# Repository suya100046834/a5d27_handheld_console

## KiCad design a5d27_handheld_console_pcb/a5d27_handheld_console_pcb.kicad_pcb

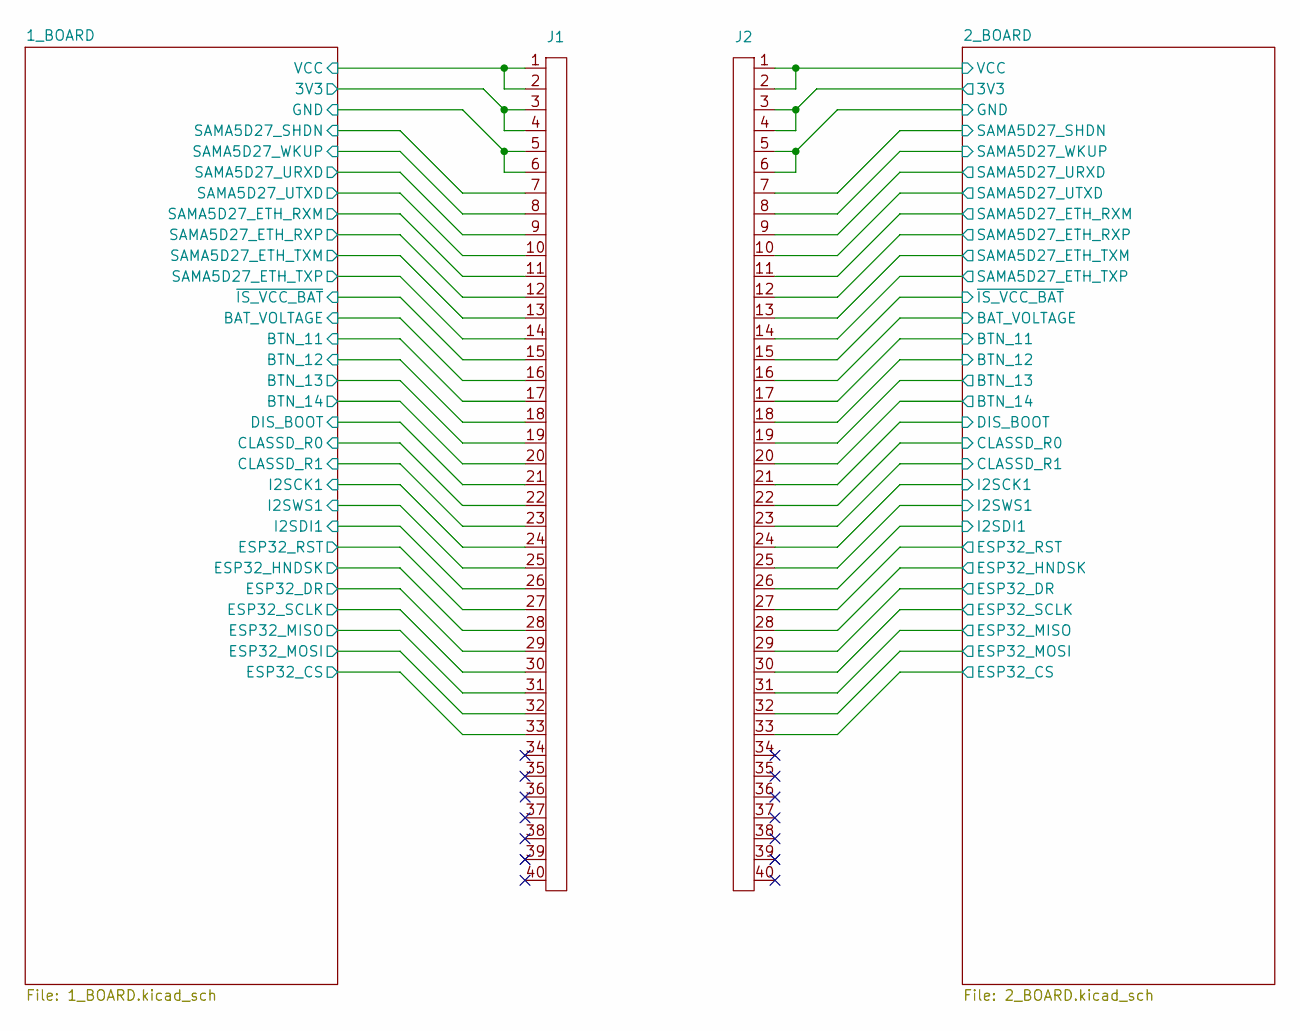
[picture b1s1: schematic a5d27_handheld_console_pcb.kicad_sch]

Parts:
J1: CONN_MALE
J2: CONN_FEMALE

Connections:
3V3_1: J1.3, J1.4; also elsewhere on the board
3V3_2: J2.3, J2.4; also elsewhere on the board
/1_BOARD/BAT_VOLTAGE: J1.16; also elsewhere on the board
/1_BOARD/BTN_11: J1.17; also elsewhere on the board
/1_BOARD/BTN_12: J1.18; also elsewhere on the board
/1_BOARD/BTN_13: J1.19; also elsewhere on the board
/1_BOARD/BTN_14: J1.20; also elsewhere on the board
/1_BOARD/CLASSD_R0: J1.22; also elsewhere on the board
/1_BOARD/CLASSD_R1: J1.23; also elsewhere on the board
/1_BOARD/DIS_BOOT: J1.21; also elsewhere on the board
/1_BOARD/ESP32_CS: J1.33; also elsewhere on the board
/1_BOARD/ESP32_DR: J1.29; also elsewhere on the board
/1_BOARD/ESP32_HNDSK: J1.28; also elsewhere on the board
/1_BOARD/ESP32_MISO: J1.31; also elsewhere on the board
/1_BOARD/ESP32_MOSI: J1.32; also elsewhere on the board
/1_BOARD/ESP32_RST: J1.27; also elsewhere on the board
/1_BOARD/ESP32_SCLK: J1.30; also elsewhere on the board
/1_BOARD/I2SCK1: J1.24; also elsewhere on the board
/1_BOARD/I2SDI1: J1.26; also elsewhere on the board
/1_BOARD/I2SWS1: J1.25; also elsewhere on the board
/1_BOARD/SAMA5D27_ETH_RXM: J1.11; also elsewhere on the board
/1_BOARD/SAMA5D27_ETH_RXP: J1.12; also elsewhere on the board
/1_BOARD/SAMA5D27_ETH_TXM: J1.13; also elsewhere on the board
/1_BOARD/SAMA5D27_ETH_TXP: J1.14; also elsewhere on the board
/1_BOARD/SAMA5D27_SHDN: J1.7; also elsewhere on the board
/1_BOARD/SAMA5D27_URXD: J1.9; also elsewhere on the board
/1_BOARD/SAMA5D27_UTXD: J1.10; also elsewhere on the board
/1_BOARD/SAMA5D27_WKUP: J1.8; also elsewhere on the board
/1_BOARD/~IS_VCC_BAT: J1.15; also elsewhere on the board
/2_BOARD/BAT_VOLTAGE: J2.16; also elsewhere on the board
/2_BOARD/BTN_11: J2.17; also elsewhere on the board
/2_BOARD/BTN_12: J2.18; also elsewhere on the board
/2_BOARD/BTN_13: J2.19; also elsewhere on the board
/2_BOARD/BTN_14: J2.20; also elsewhere on the board
/2_BOARD/CLASSD_R0: J2.22; also elsewhere on the board
/2_BOARD/CLASSD_R1: J2.23; also elsewhere on the board
/2_BOARD/DIS_BOOT: J2.21; also elsewhere on the board
/2_BOARD/ESP32_CS: J2.33; also elsewhere on the board
/2_BOARD/ESP32_DR: J2.29; also elsewhere on the board
/2_BOARD/ESP32_HNDSK: J2.28; also elsewhere on the board
/2_BOARD/ESP32_MISO: J2.31; also elsewhere on the board
/2_BOARD/ESP32_MOSI: J2.32; also elsewhere on the board
/2_BOARD/ESP32_RST: J2.27; also elsewhere on the board
/2_BOARD/ESP32_SCLK: J2.30; also elsewhere on the board
/2_BOARD/I2SCK1: J2.24; also elsewhere on the board
/2_BOARD/I2SDI1: J2.26; also elsewhere on the board
/2_BOARD/I2SWS1: J2.25; also elsewhere on the board
/2_BOARD/SAMA5D27_ETH_RXM: J2.11; also elsewhere on the board
/2_BOARD/SAMA5D27_ETH_RXP: J2.12; also elsewhere on the board
/2_BOARD/SAMA5D27_ETH_TXM: J2.13; also elsewhere on the board
/2_BOARD/SAMA5D27_ETH_TXP: J2.14; also elsewhere on the board
/2_BOARD/SAMA5D27_SHDN: J2.7; also elsewhere on the board
/2_BOARD/SAMA5D27_URXD: J2.9; also elsewhere on the board
/2_BOARD/SAMA5D27_UTXD: J2.10; also elsewhere on the board
/2_BOARD/SAMA5D27_WKUP: J2.8; also elsewhere on the board
/2_BOARD/~IS_VCC_BAT: J2.15; also elsewhere on the board
GND_1: J1.5, J1.6; also elsewhere on the board
GND_2: J2.5, J2.6; also elsewhere on the board
VCC_1: J1.1, J1.2; also elsewhere on the board
VCC_2: J2.1, J2.2; also elsewhere on the board

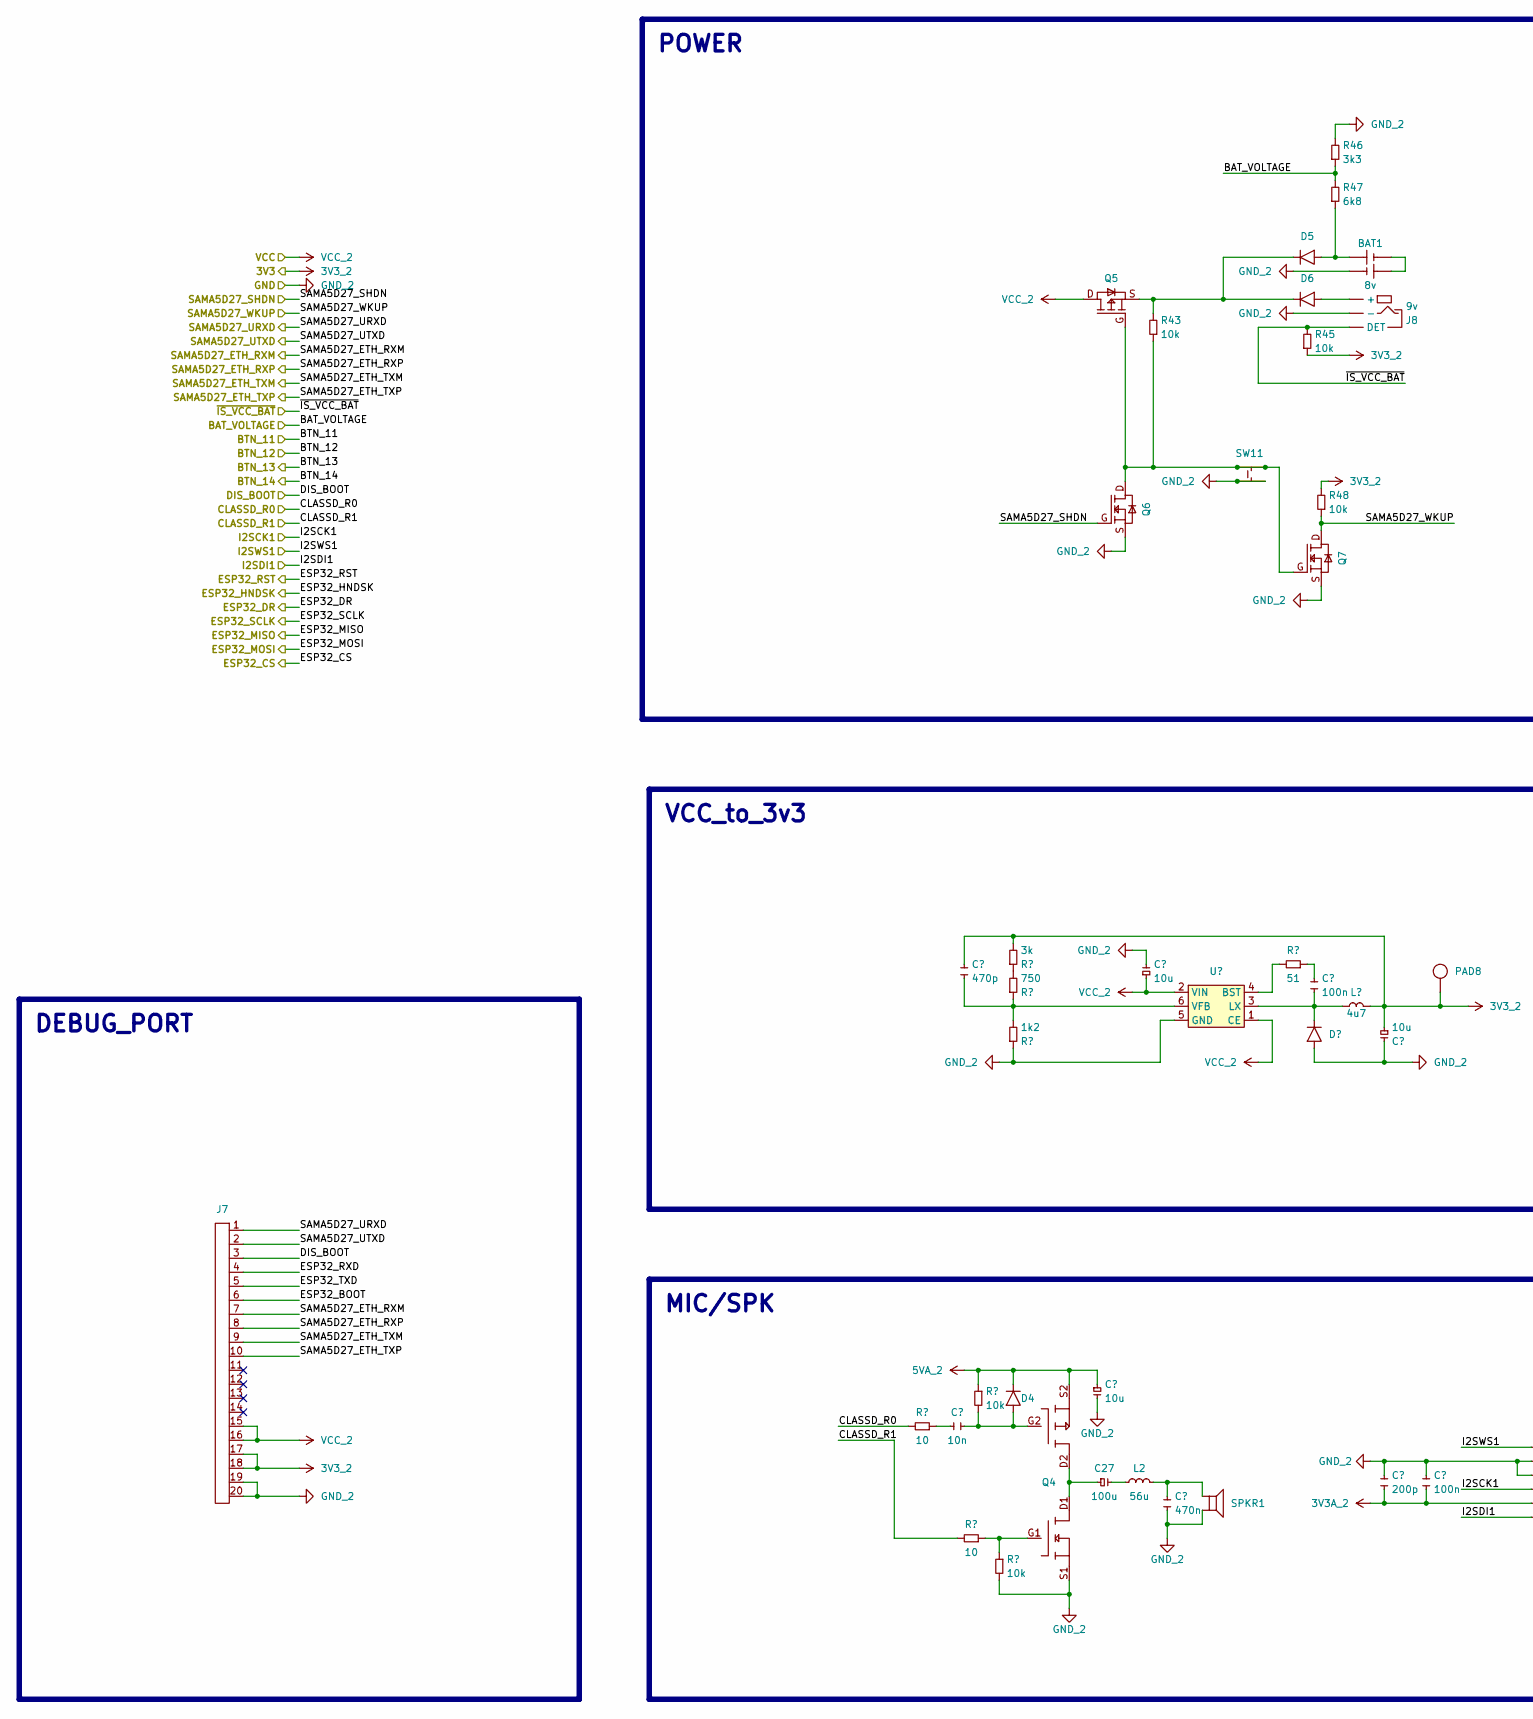
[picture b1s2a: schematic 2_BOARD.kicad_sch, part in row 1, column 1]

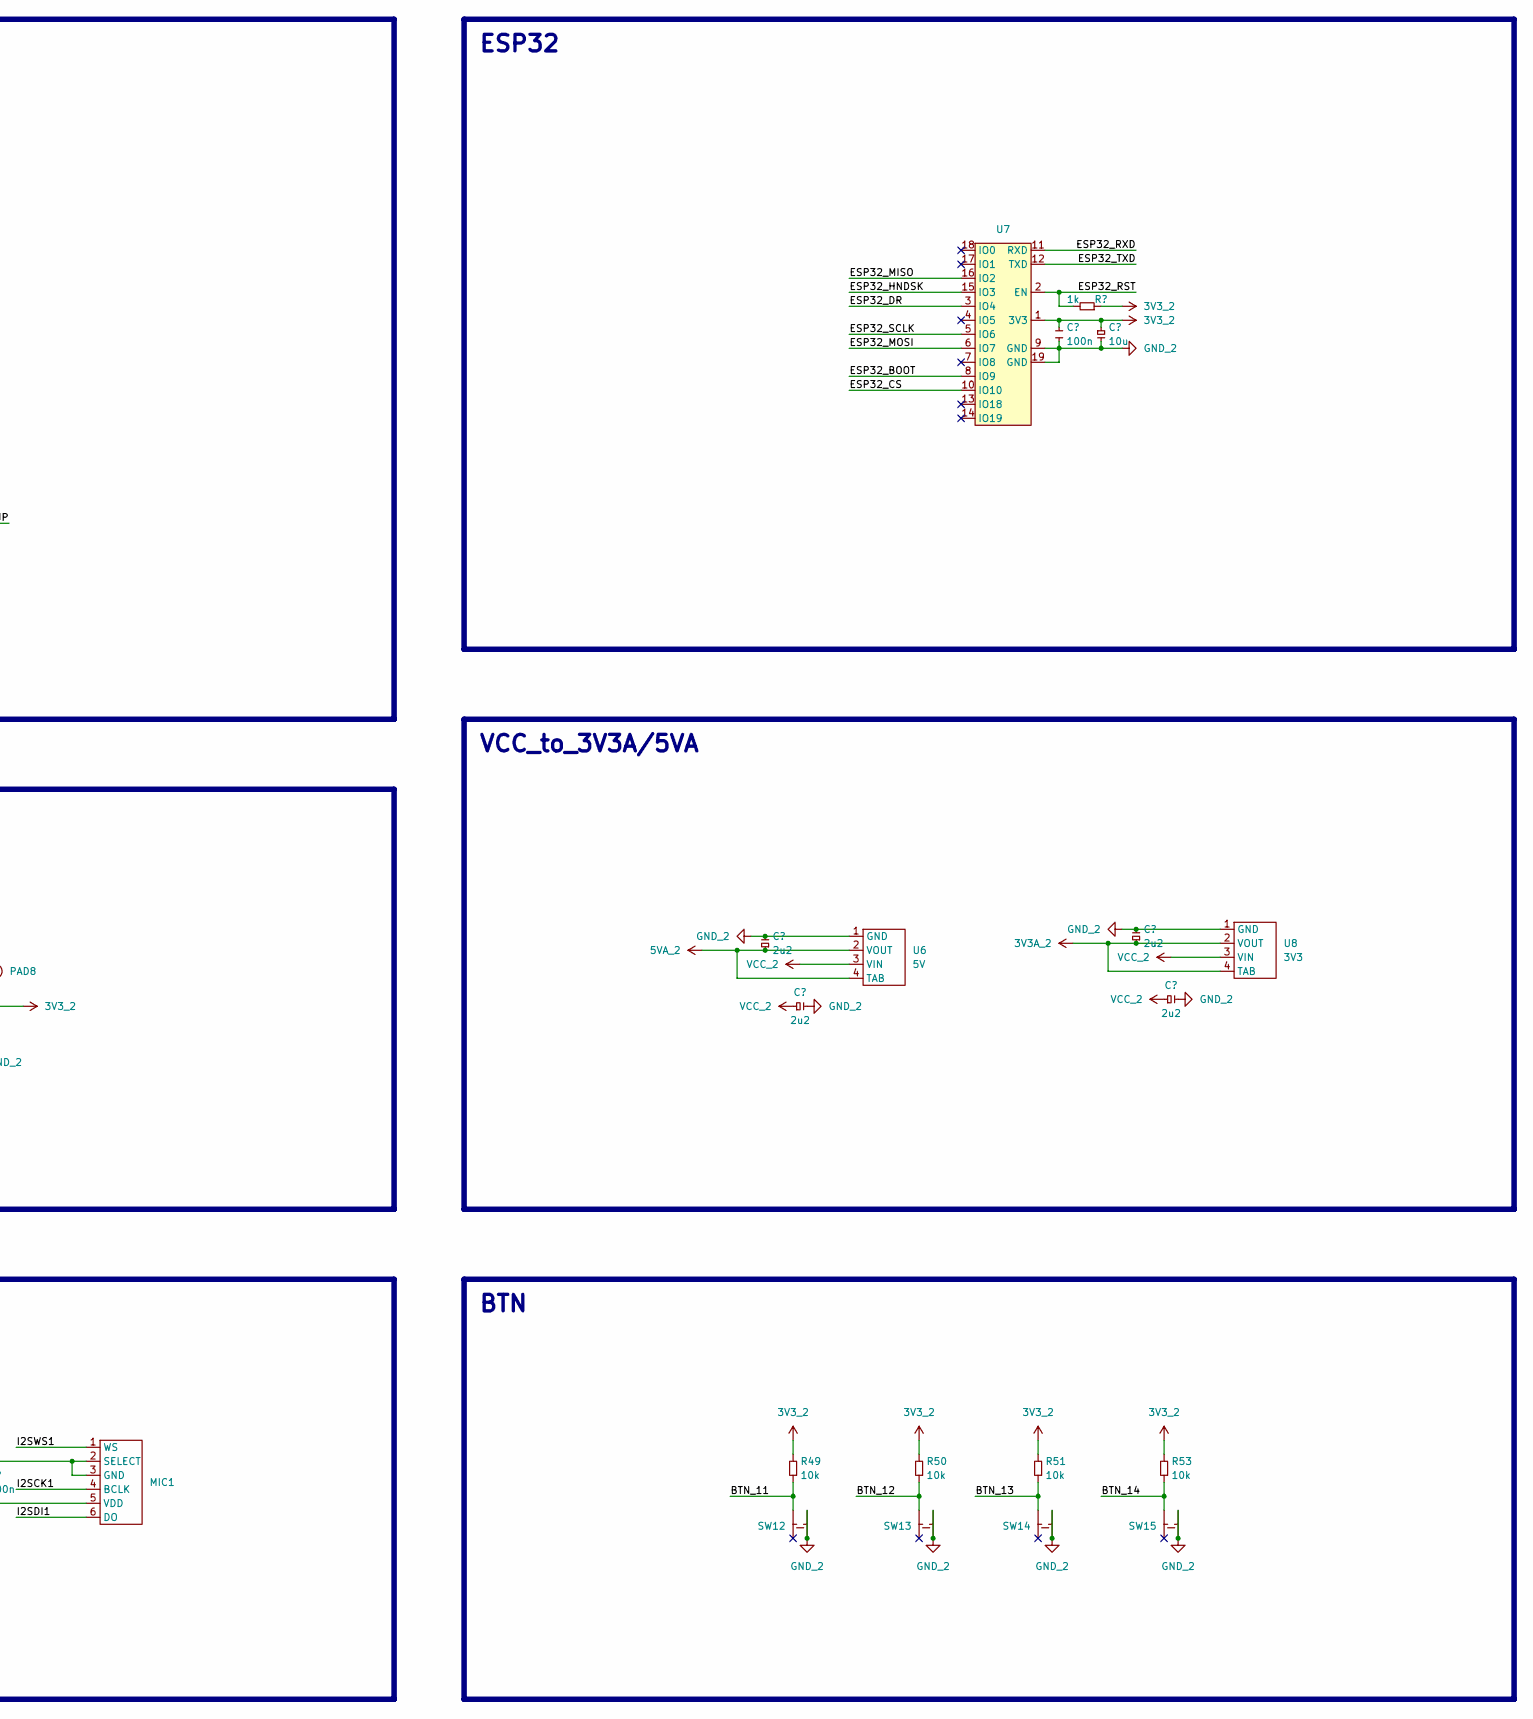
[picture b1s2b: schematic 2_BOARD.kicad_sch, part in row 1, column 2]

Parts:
BAT1: 8v; BAT
C24: 10n; C_Ceramic_2012
C25: 470p; C_Ceramic_2012
C26, C28, C31, C37: 10u; C_Tantalum_3216
C27: 100u; CAP_6.3pix5.3mm
C29: 470n; C_Ceramic_2012
C30, C33, C36: 100n; C_Ceramic_2012
C32: 200p; C_Ceramic_2012
C34, C35, C38, C39: 2u2; C_Tantalum_3216
D4, D7: CMS06
D5, D6: ES2DA-13-F
J7: DEBUG_PORT
J8: 9v; DC_JACK
L2: 56u; LQH3NPH560MMEL
L3: 4u7; DFE252012F-4R7M
MIC1: SPH0645LM4H-B
PAD8: PAD
Q4: DMC2400UV
Q5: DMP3099L
Q6, Q7: N-FET
R36, R37: 10; R_2012
R38, R42, R43, R45, R48, R49, R50, R51, R53: 10k; R_2012
R39: 3k; R_2012
R40: 750; R_2012
R41: 1k2; R_2012
R44: 51; R_2012
R46: 3k3; R_2012
R47: 6k8; R_2012
R52: 1k; R_2012
SPKR1: SPEAKER
SW11, SW12, SW13, SW14, SW15: EVQ-P7A01P
U5: R1240N001B
U6: 5V; 1117
U7: ESP32-C3-WROOM-02
U8: 3V3; 1117

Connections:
3V3A_2: C32.2, C33.2, C38.1, MIC1.5 (VDD), U8.2 (VOUT), U8.4 (TAB)
3V3_2: C25.2, C31.1, C36.2, C37.1, J7.17, J7.18, L3.2, PAD8.1, R39.2, R45.1, R48.2, R49.2, R50.2, R51.2, R52.1, R53.2, U7.1 (3V3); also elsewhere on the board
5VA_2: C26.1, C34.1, D4.2, Q4.S2, R38.1, U6.2 (VOUT), U6.4 (TAB)
/2_BOARD/BAT_VOLTAGE: R46.1, R47.2; also elsewhere on the board
/2_BOARD/BTN_11: R49.1, SW12.3; also elsewhere on the board
/2_BOARD/BTN_12: R50.1, SW13.3; also elsewhere on the board
/2_BOARD/BTN_13: R51.1, SW14.3; also elsewhere on the board
/2_BOARD/BTN_14: R53.1, SW15.3; also elsewhere on the board
/2_BOARD/CLASSD_R0: R36.2; also elsewhere on the board
/2_BOARD/CLASSD_R1: R37.2; also elsewhere on the board
/2_BOARD/DIS_BOOT: J7.3; also elsewhere on the board
/2_BOARD/ESP32_BOOT: J7.6, U7.8 (IO9)
/2_BOARD/ESP32_CS: U7.10 (IO10); also elsewhere on the board
/2_BOARD/ESP32_DR: U7.3 (IO4); also elsewhere on the board
/2_BOARD/ESP32_HNDSK: U7.15 (IO3); also elsewhere on the board
/2_BOARD/ESP32_MISO: U7.16 (IO2); also elsewhere on the board
/2_BOARD/ESP32_MOSI: U7.6 (IO7); also elsewhere on the board
/2_BOARD/ESP32_RST: R52.2, U7.2 (EN); also elsewhere on the board
/2_BOARD/ESP32_RXD: J7.4, U7.11 (RXD)
/2_BOARD/ESP32_SCLK: U7.5 (IO6); also elsewhere on the board
/2_BOARD/ESP32_TXD: J7.5, U7.12 (TXD)
/2_BOARD/I2SCK1: MIC1.4 (BCLK); also elsewhere on the board
/2_BOARD/I2SDI1: MIC1.6 (DO); also elsewhere on the board
/2_BOARD/I2SWS1: MIC1.1 (WS); also elsewhere on the board
/2_BOARD/SAMA5D27_ETH_RXM: J7.7; also elsewhere on the board
/2_BOARD/SAMA5D27_ETH_RXP: J7.8; also elsewhere on the board
/2_BOARD/SAMA5D27_ETH_TXM: J7.9; also elsewhere on the board
/2_BOARD/SAMA5D27_ETH_TXP: J7.10; also elsewhere on the board
/2_BOARD/SAMA5D27_SHDN: Q6.G; also elsewhere on the board
/2_BOARD/SAMA5D27_URXD: J7.1; also elsewhere on the board
/2_BOARD/SAMA5D27_UTXD: J7.2; also elsewhere on the board
/2_BOARD/SAMA5D27_WKUP: Q7.D, R48.1; also elsewhere on the board
/2_BOARD/~IS_VCC_BAT: J8.3 (DET), R45.2; also elsewhere on the board
GND_2: BAT1.3, C26.2, C28.2, C29.2, C31.2, C32.1, C33.1, C34.2, C35.2, C36.1, C37.2, C38.2, C39.2, D7.1, J7.19, J7.20, J8.2 (-), MIC1.2 (SELECT), MIC1.3 (GND), Q4.S1, Q6.S, Q7.S, R41.1, R42.2, R46.2, SPKR1.2, SW11.1, SW11.2, SW12.1, SW12.2, SW13.1, SW13.2, SW14.1, SW14.2, SW15.1, SW15.2, U5.5 (GND), U6.1 (GND), U7.9 (GND), U7.19 (GND), U8.1 (GND); also elsewhere on the board
unnamed: BAT1.1, D5.1, R47.1
unnamed: BAT1.2, BAT1.4
unnamed: C24.1, D4.1, Q4.G2, R38.2
unnamed: C24.2, R36.1
unnamed: C27.1, Q4.D1, Q4.D2
unnamed: C27.2, L2.1
unnamed: C29.1, L2.2, SPKR1.1
unnamed: C30.2, R44.1
unnamed: D5.2, D6.2, Q5.S, R43.2
unnamed: D6.1, J8.1 (+)
unnamed: Q4.G1, R37.1, R42.1
unnamed: Q5.G, Q6.D, Q7.G, R43.1, SW11.3, SW11.4
unnamed: R39.1, R40.2
unnamed: R44.2, U5.4 (BST)
unnamed: C30.1, D7.2, L3.1, U5.3 (LX)
unnamed: C25.1, R40.1, R41.2, U5.6 (VFB)
VCC_2: C28.1, C35.1, C39.1, J7.15, J7.16, Q5.D, U5.1 (CE), U5.2 (VIN), U6.3 (VIN), U8.3 (VIN); also elsewhere on the board

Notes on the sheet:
MIC/SPK
POWER
DEBUG_PORT
ESP32
BTN
VCC_to_3V3A/5VA
VCC_to_3v3

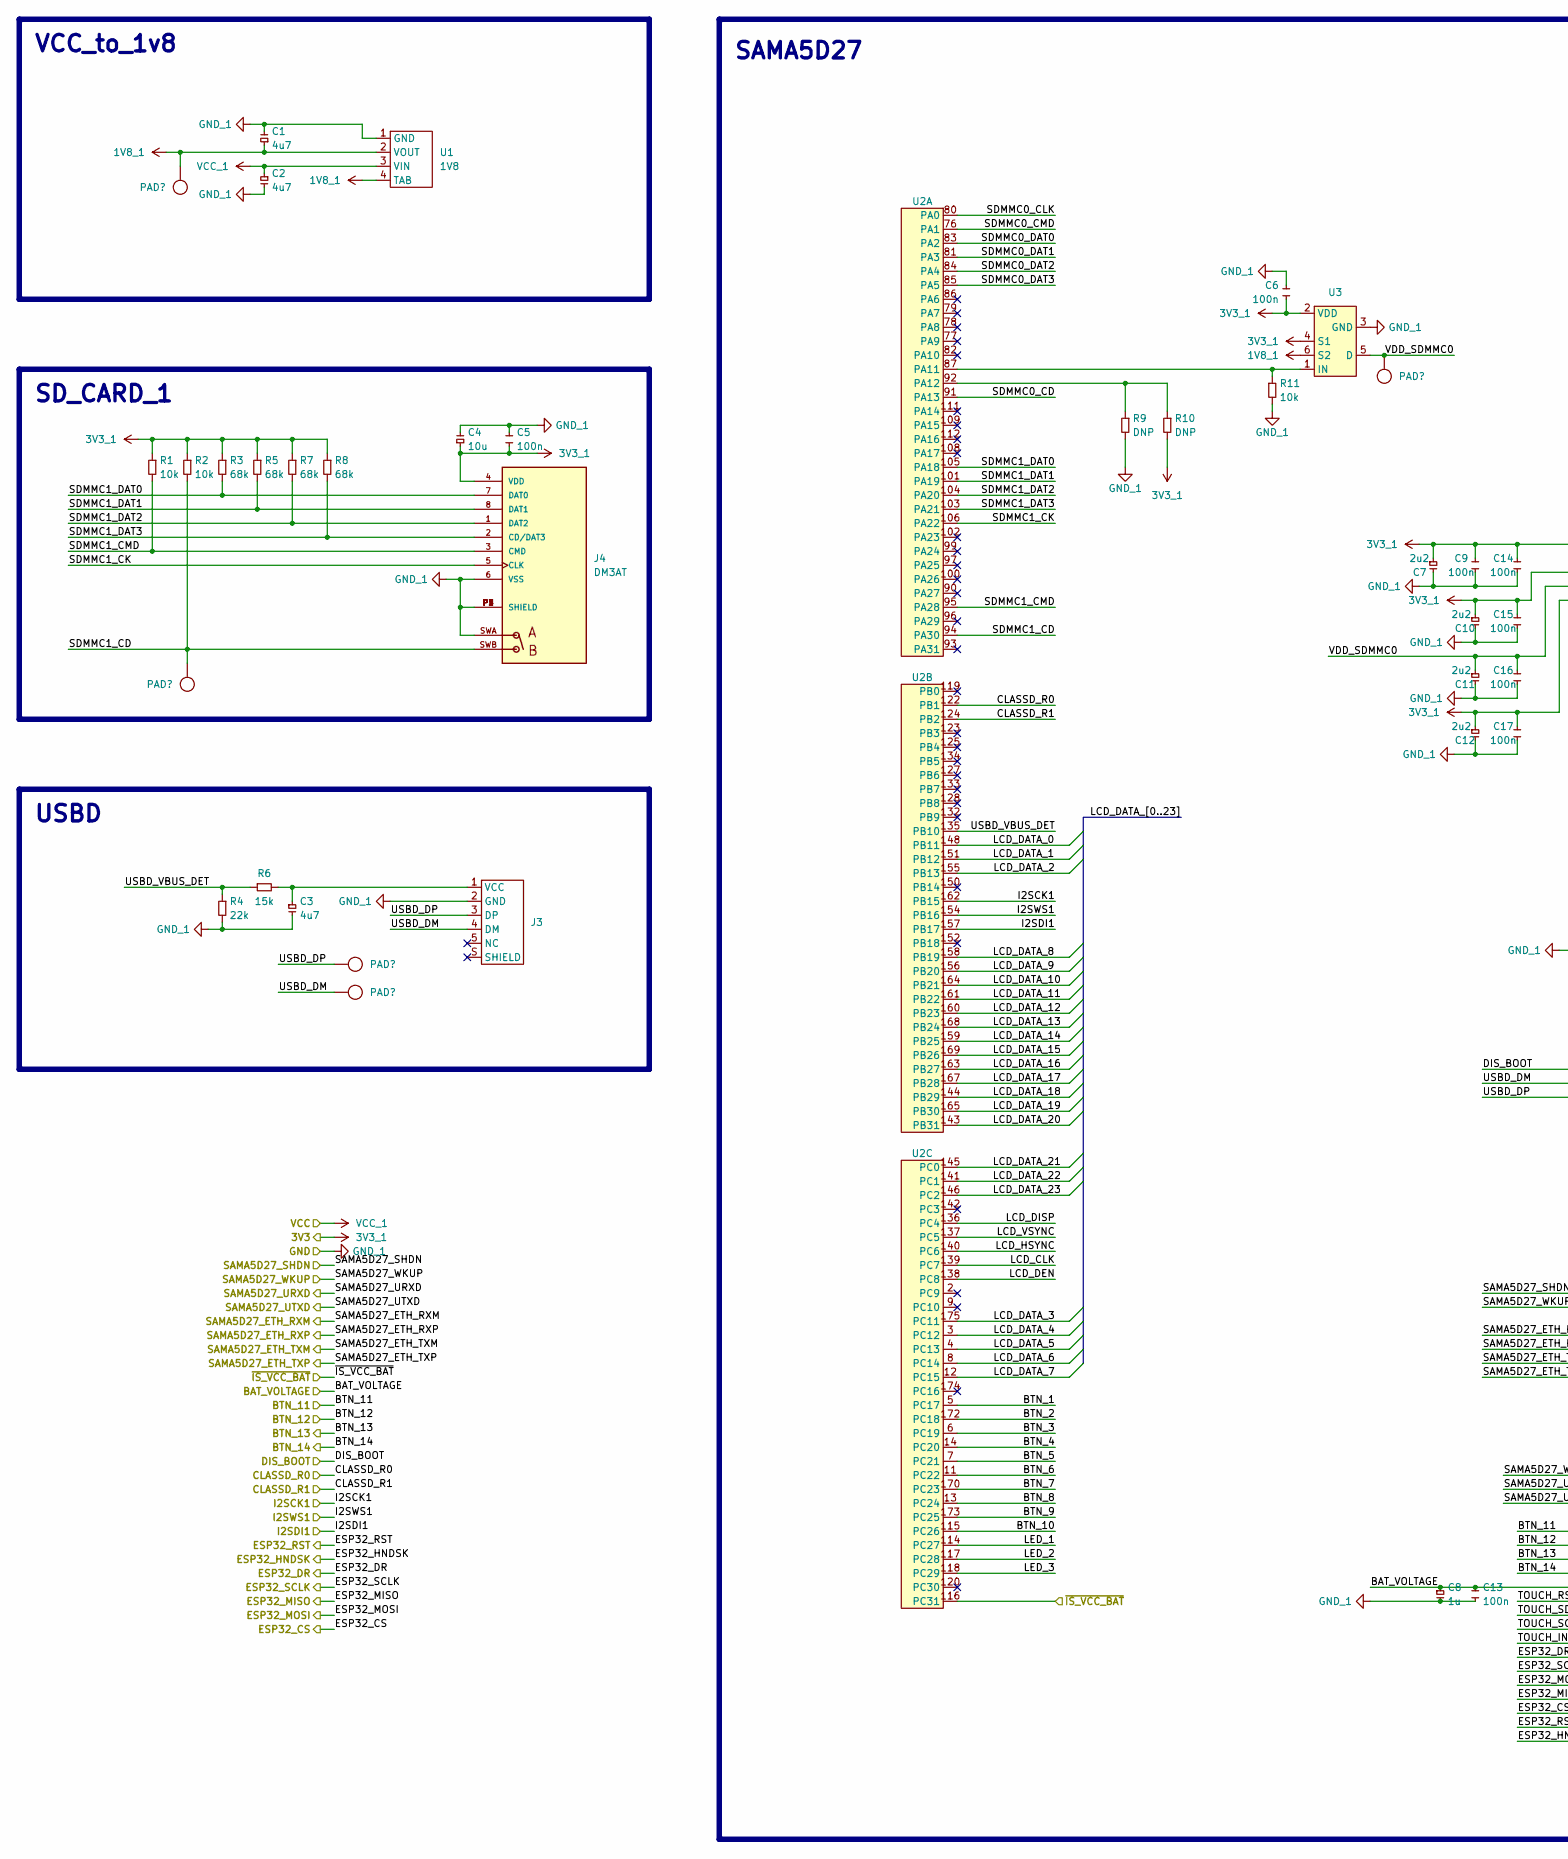
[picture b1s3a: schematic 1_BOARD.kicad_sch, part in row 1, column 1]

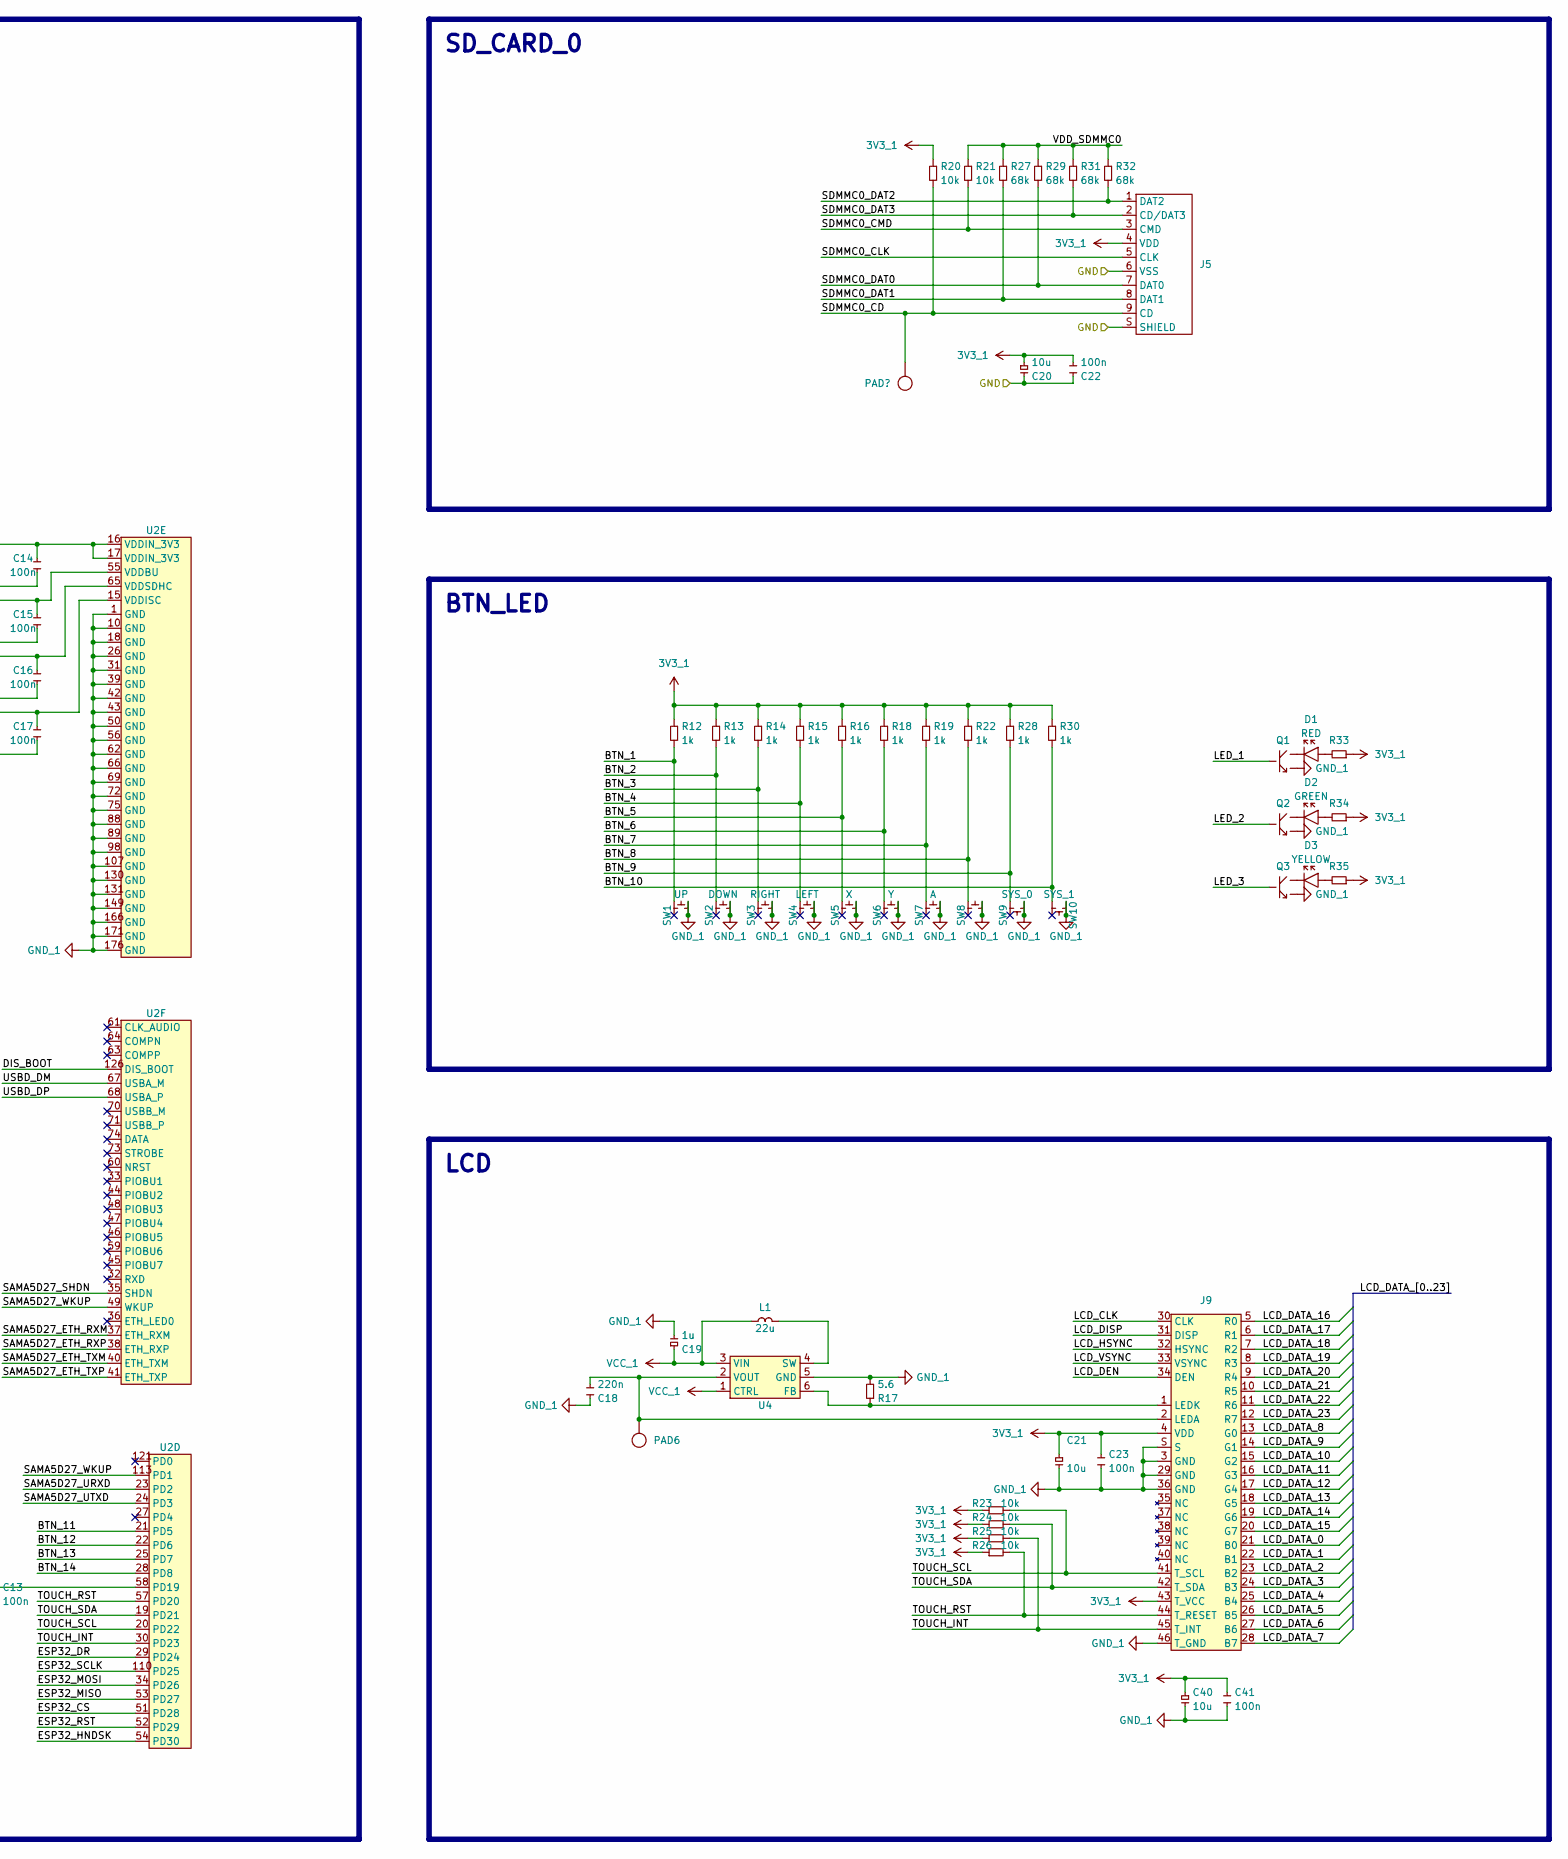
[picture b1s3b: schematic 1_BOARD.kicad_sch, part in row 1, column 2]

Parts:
C1, C2, C3: 4u7; C_Tantalum_3216
C4, C20, C21, C40: 10u; C_Tantalum_3216
C5, C6, C9, C13, C14, C15, C16, C17, C22, C23, C41: 100n; C_Ceramic_2012
C7, C10, C11, C12: 2u2; C_Tantalum_3216
C8, C19: 1u; C_Tantalum_3216
C18: 220n; C_Ceramic_2012
D1: RED; LED_2012
D2: GREEN; LED_2012
D3: YELLOW; LED_2012
J3: USB_B
J4: DM3AT; HRS_DM3AT-SF-PEJM5
J5: DM3CS
J9: ER-TFT043-7
L1: 22u; NLCV25T-220K-PF
PAD1, PAD2, PAD3, PAD4, PAD5, PAD6, PAD7: PAD
Q1, Q2, Q3: MMBT3904
R1, R2, R11, R20, R21, R23, R24, R25, R26: 10k; R_2012
R3, R5, R7, R8, R27, R29, R31, R32: 68k; R_2012
R4: 22k; R_2012
R6: 15k; R_2012
R9, R10: DNP; R_2012
R12, R13, R14, R15, R16, R18, R19, R22, R28, R30: 1k; R_2012
R17: 5.6; R_2012
R33, R34, R35: R_2012
SW1: UP; SWITCH
SW2: DOWN; SWITCH
SW3: RIGHT; SWITCH
SW4: LEFT; SWITCH
SW5: X; SWITCH
SW6: Y; SWITCH
SW7: A; SWITCH
SW8: B; SWITCH
SW9: SYS_0; SWITCH
SW10: SYS_1; SWITCH
U1: 1V8; 1117
U2: ATSAMA5D27-SOM1
U3: ADG849
U4: AP3036B

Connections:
1V8_1: C1.1, PAD1.1, U1.2 (VOUT), U1.4 (TAB), U3.6 (S2)
3V3_1: C4.1, C5.2, C6.1, C7.1, C9.2, C10.1, C12.1, C14.2, C15.2, C17.2, C20.1, C21.1, C22.2, C23.2, C40.1, C41.2, J4.4 (VDD), J5.4 (VDD), J9.4 (VDD), J9.43 (T_VCC), R1.1, R2.1, R3.1, R5.1, R7.1, R8.1, R10.2, R12.1, R13.1, R14.1, R15.1, R16.1, R18.1, R19.1, R20.1, R22.1, R23.1, R24.1, R25.1, R26.1, R28.1, R30.1, R33.1, R34.1, R35.1, U2.15 (VDDISC), U2.16 (VDDIN_3V3), U2.17 (VDDIN_3V3), U2.55 (VDDBU), U3.2 (VDD), U3.4 (S1); also elsewhere on the board
/1_BOARD/BAT_VOLTAGE: C8.1, C13.2, U2.58 (PD19); also elsewhere on the board
/1_BOARD/BTN_1: R12.2, SW1.2, U2.5 (PC17); also elsewhere on the board
/1_BOARD/BTN_2: R13.2, SW2.2, U2.172 (PC18); also elsewhere on the board
/1_BOARD/BTN_3: R14.2, SW3.2, U2.6 (PC19); also elsewhere on the board
/1_BOARD/BTN_4: R15.2, SW4.2, U2.14 (PC20); also elsewhere on the board
/1_BOARD/BTN_5: R16.2, SW5.2, U2.7 (PC21); also elsewhere on the board
/1_BOARD/BTN_6: R18.2, SW6.2, U2.11 (PC22); also elsewhere on the board
/1_BOARD/BTN_7: R19.2, SW7.2, U2.170 (PC23); also elsewhere on the board
/1_BOARD/BTN_8: R22.2, SW8.2, U2.13 (PC24); also elsewhere on the board
/1_BOARD/BTN_9: R28.2, SW9.1, U2.173 (PC25)
/1_BOARD/BTN_10: R30.2, SW10.3, U2.115 (PC26)
/1_BOARD/BTN_11: U2.21 (PD5); also elsewhere on the board
/1_BOARD/BTN_12: U2.22 (PD6); also elsewhere on the board
/1_BOARD/BTN_13: U2.25 (PD7); also elsewhere on the board
/1_BOARD/BTN_14: U2.28 (PD8); also elsewhere on the board
/1_BOARD/CLASSD_R0: U2.122 (PB1); also elsewhere on the board
/1_BOARD/CLASSD_R1: U2.124 (PB2); also elsewhere on the board
/1_BOARD/DIS_BOOT: U2.126 (DIS_BOOT); also elsewhere on the board
/1_BOARD/ESP32_CS: U2.51 (PD28); also elsewhere on the board
/1_BOARD/ESP32_DR: U2.29 (PD24); also elsewhere on the board
/1_BOARD/ESP32_HNDSK: U2.54 (PD30); also elsewhere on the board
/1_BOARD/ESP32_MISO: U2.53 (PD27); also elsewhere on the board
/1_BOARD/ESP32_MOSI: U2.34 (PD26); also elsewhere on the board
/1_BOARD/ESP32_RST: U2.52 (PD29); also elsewhere on the board
/1_BOARD/ESP32_SCLK: U2.110 (PD25); also elsewhere on the board
/1_BOARD/I2SCK1: U2.162 (PB15); also elsewhere on the board
/1_BOARD/I2SDI1: U2.157 (PB17); also elsewhere on the board
/1_BOARD/I2SWS1: U2.154 (PB16); also elsewhere on the board
/1_BOARD/LCD_CLK: J9.30 (CLK), U2.139 (PC7)
/1_BOARD/LCD_DATA_0: J9.21 (B0), U2.148 (PB11)
/1_BOARD/LCD_DATA_1: J9.22 (B1), U2.151 (PB12)
/1_BOARD/LCD_DATA_2: J9.23 (B2), U2.155 (PB13)
/1_BOARD/LCD_DATA_3: J9.24 (B3), U2.175 (PC11)
/1_BOARD/LCD_DATA_4: J9.25 (B4), U2.3 (PC12)
/1_BOARD/LCD_DATA_5: J9.26 (B5), U2.4 (PC13)
/1_BOARD/LCD_DATA_6: J9.27 (B6), U2.8 (PC14)
/1_BOARD/LCD_DATA_7: J9.28 (B7), U2.12 (PC15)
/1_BOARD/LCD_DATA_8: J9.13 (G0), U2.158 (PB19)
/1_BOARD/LCD_DATA_9: J9.14 (G1), U2.156 (PB20)
/1_BOARD/LCD_DATA_10: J9.15 (G2), U2.164 (PB21)
/1_BOARD/LCD_DATA_11: J9.16 (G3), U2.161 (PB22)
/1_BOARD/LCD_DATA_12: J9.17 (G4), U2.160 (PB23)
/1_BOARD/LCD_DATA_13: J9.18 (G5), U2.168 (PB24)
/1_BOARD/LCD_DATA_14: J9.19 (G6), U2.159 (PB25)
/1_BOARD/LCD_DATA_15: J9.20 (G7), U2.169 (PB26)
/1_BOARD/LCD_DATA_16: J9.5 (R0), U2.163 (PB27)
/1_BOARD/LCD_DATA_17: J9.6 (R1), U2.167 (PB28)
/1_BOARD/LCD_DATA_18: J9.7 (R2), U2.144 (PB29)
/1_BOARD/LCD_DATA_19: J9.8 (R3), U2.165 (PB30)
/1_BOARD/LCD_DATA_20: J9.9 (R4), U2.143 (PB31)
/1_BOARD/LCD_DATA_21: J9.10 (R5), U2.145 (PC0)
/1_BOARD/LCD_DATA_22: J9.11 (R6), U2.141 (PC1)
/1_BOARD/LCD_DATA_23: J9.12 (R7), U2.146 (PC2)
/1_BOARD/LCD_DEN: J9.34 (DEN), U2.138 (PC8)
/1_BOARD/LCD_DISP: J9.31 (DISP), U2.136 (PC4)
/1_BOARD/LCD_HSYNC: J9.32 (HSYNC), U2.140 (PC6)
/1_BOARD/LCD_VSYNC: J9.33 (VSYNC), U2.137 (PC5)
/1_BOARD/LED_1: Q1.1 (B), U2.114 (PC27)
/1_BOARD/LED_2: Q2.1 (B), U2.117 (PC28)
/1_BOARD/LED_3: Q3.1 (B), U2.118 (PC29)
/1_BOARD/SAMA5D27_ETH_RXM: U2.37 (ETH_RXM); also elsewhere on the board
/1_BOARD/SAMA5D27_ETH_RXP: U2.38 (ETH_RXP); also elsewhere on the board
/1_BOARD/SAMA5D27_ETH_TXM: U2.40 (ETH_TXM); also elsewhere on the board
/1_BOARD/SAMA5D27_ETH_TXP: U2.41 (ETH_TXP); also elsewhere on the board
/1_BOARD/SAMA5D27_SHDN: U2.35 (SHDN); also elsewhere on the board
/1_BOARD/SAMA5D27_URXD: U2.23 (PD2); also elsewhere on the board
/1_BOARD/SAMA5D27_UTXD: U2.24 (PD3); also elsewhere on the board
/1_BOARD/SAMA5D27_WKUP: U2.49 (WKUP), U2.113 (PD1); also elsewhere on the board
/1_BOARD/SDMMC0_CD: J5.9 (CD), PAD7.1, R20.2, U2.91 (PA13)
/1_BOARD/SDMMC0_CLK: J5.5 (CLK), U2.80 (PA0)
/1_BOARD/SDMMC0_CMD: J5.3 (CMD), R21.2, U2.76 (PA1)
/1_BOARD/SDMMC0_DAT0: J5.7 (DAT0), R29.2, U2.83 (PA2)
/1_BOARD/SDMMC0_DAT1: J5.8 (DAT1), R27.2, U2.81 (PA3)
/1_BOARD/SDMMC0_DAT2: J5.1 (DAT2), R32.2, U2.84 (PA4)
/1_BOARD/SDMMC0_DAT3: J5.2 (CD/DAT3), R31.2, U2.85 (PA5)
/1_BOARD/SDMMC1_CD: J4.SWB, PAD2.1, R2.2, U2.94 (PA30)
/1_BOARD/SDMMC1_CK: J4.5 (CLK), U2.106 (PA22)
/1_BOARD/SDMMC1_CMD: J4.3 (CMD), R1.2, U2.95 (PA28)
/1_BOARD/SDMMC1_DAT0: J4.7 (DAT0), R3.2, U2.105 (PA18)
/1_BOARD/SDMMC1_DAT1: J4.8 (DAT1), R5.2, U2.101 (PA19)
/1_BOARD/SDMMC1_DAT2: J4.1 (DAT2), R7.2, U2.104 (PA20)
/1_BOARD/SDMMC1_DAT3: J4.2 (CD/DAT3), R8.2, U2.103 (PA21)
/1_BOARD/TOUCH_INT: J9.45 (T_INT), R25.2, U2.30 (PD23)
/1_BOARD/TOUCH_RST: J9.44 (T_RESET), R26.2, U2.57 (PD20)
/1_BOARD/TOUCH_SCL: J9.41 (T_SCL), R23.2, U2.20 (PD22)
/1_BOARD/TOUCH_SDA: J9.42 (T_SDA), R24.2, U2.19 (PD21)
/1_BOARD/USBD_DM: J3.4 (DM), PAD4.1, U2.67 (USBA_M)
/1_BOARD/USBD_DP: J3.3 (DP), PAD3.1, U2.68 (USBA_P)
/1_BOARD/USBD_VBUS_DET: R4.1, R6.1, U2.135 (PB10)
/1_BOARD/VDD_SDMMC0: C11.1, C16.2, PAD5.1, R21.1, R27.1, R29.1, R31.1, R32.1, U2.65 (VDDSDHC), U3.5 (D)
/1_BOARD/~IS_VCC_BAT: U2.116 (PC31); also elsewhere on the board
GND_1: C1.2, C2.2, C3.2, C4.2, C5.1, C6.2, C7.2, C8.2, C9.1, C10.2, C11.2, C12.2, C13.1, C14.1, C15.1, C16.1, C17.1, C18.2, C19.2, C20.2, C21.2, C22.1, C23.1, C40.2, C41.1, J3.2 (GND), J4.6 (VSS), J4.P1 (SHIELD), J4.P2 (SHIELD), J4.P3 (SHIELD), J4.P4 (SHIELD), J4.SWA, J5.6 (VSS), J5.S (SHIELD), J9.3 (GND), J9.29 (GND), J9.36 (GND), J9.46 (T_GND), J9.S, Q1.2 (E), Q2.2 (E), Q3.2 (E), R4.2, R9.2, R11.2, R17.2, SW1.3, SW1.4, SW2.3, SW2.4, SW3.3, SW3.4, SW4.3, SW4.4, SW5.3, SW5.4, SW6.3, SW6.4, SW7.3, SW7.4, SW8.3, SW8.4, SW9.3, SW9.4, SW10.1, SW10.2, U1.1 (GND), U2.1 (GND), U2.10 (GND), U2.18 (GND), U2.26 (GND), U2.31 (GND), U2.39 (GND), U2.42 (GND), U2.43 (GND), U2.50 (GND), U2.56 (GND), U2.62 (GND), U2.66 (GND), U2.69 (GND), U2.72 (GND), U2.75 (GND), U2.88 (GND), U2.89 (GND), U2.98 (GND), U2.107 (GND), U2.130 (GND), U2.131 (GND), U2.149 (GND), U2.166 (GND), U2.171 (GND), U2.176 (GND), U3.3 (GND), U4.5 (GND); also elsewhere on the board
unnamed: D1.1, R33.2
unnamed: D2.1, R34.2
unnamed: D3.1, R35.2
unnamed: C3.1, J3.1 (VCC), R6.2
unnamed: C18.1, J9.2 (LEDA), PAD6.1, U4.2 (VOUT)
unnamed: J9.1 (LEDK), R17.1, U4.6 (FB)
unnamed: D1.2, Q1.3 (C)
unnamed: D2.2, Q2.3 (C)
unnamed: D3.2, Q3.3 (C)
unnamed: R11.1, U2.87 (PA11), U3.1 (IN)
unnamed: R9.1, R10.1, U2.92 (PA12)
unnamed: L1.2, U4.4 (SW)
VCC_1: C2.1, C19.1, L1.1, U1.3 (VIN), U4.1 (CTRL), U4.3 (VIN); also elsewhere on the board

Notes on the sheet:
LCD
BTN_LED
USBD
SD_CARD_0
VCC_to_1v8
SD_CARD_1
SAMA5D27
